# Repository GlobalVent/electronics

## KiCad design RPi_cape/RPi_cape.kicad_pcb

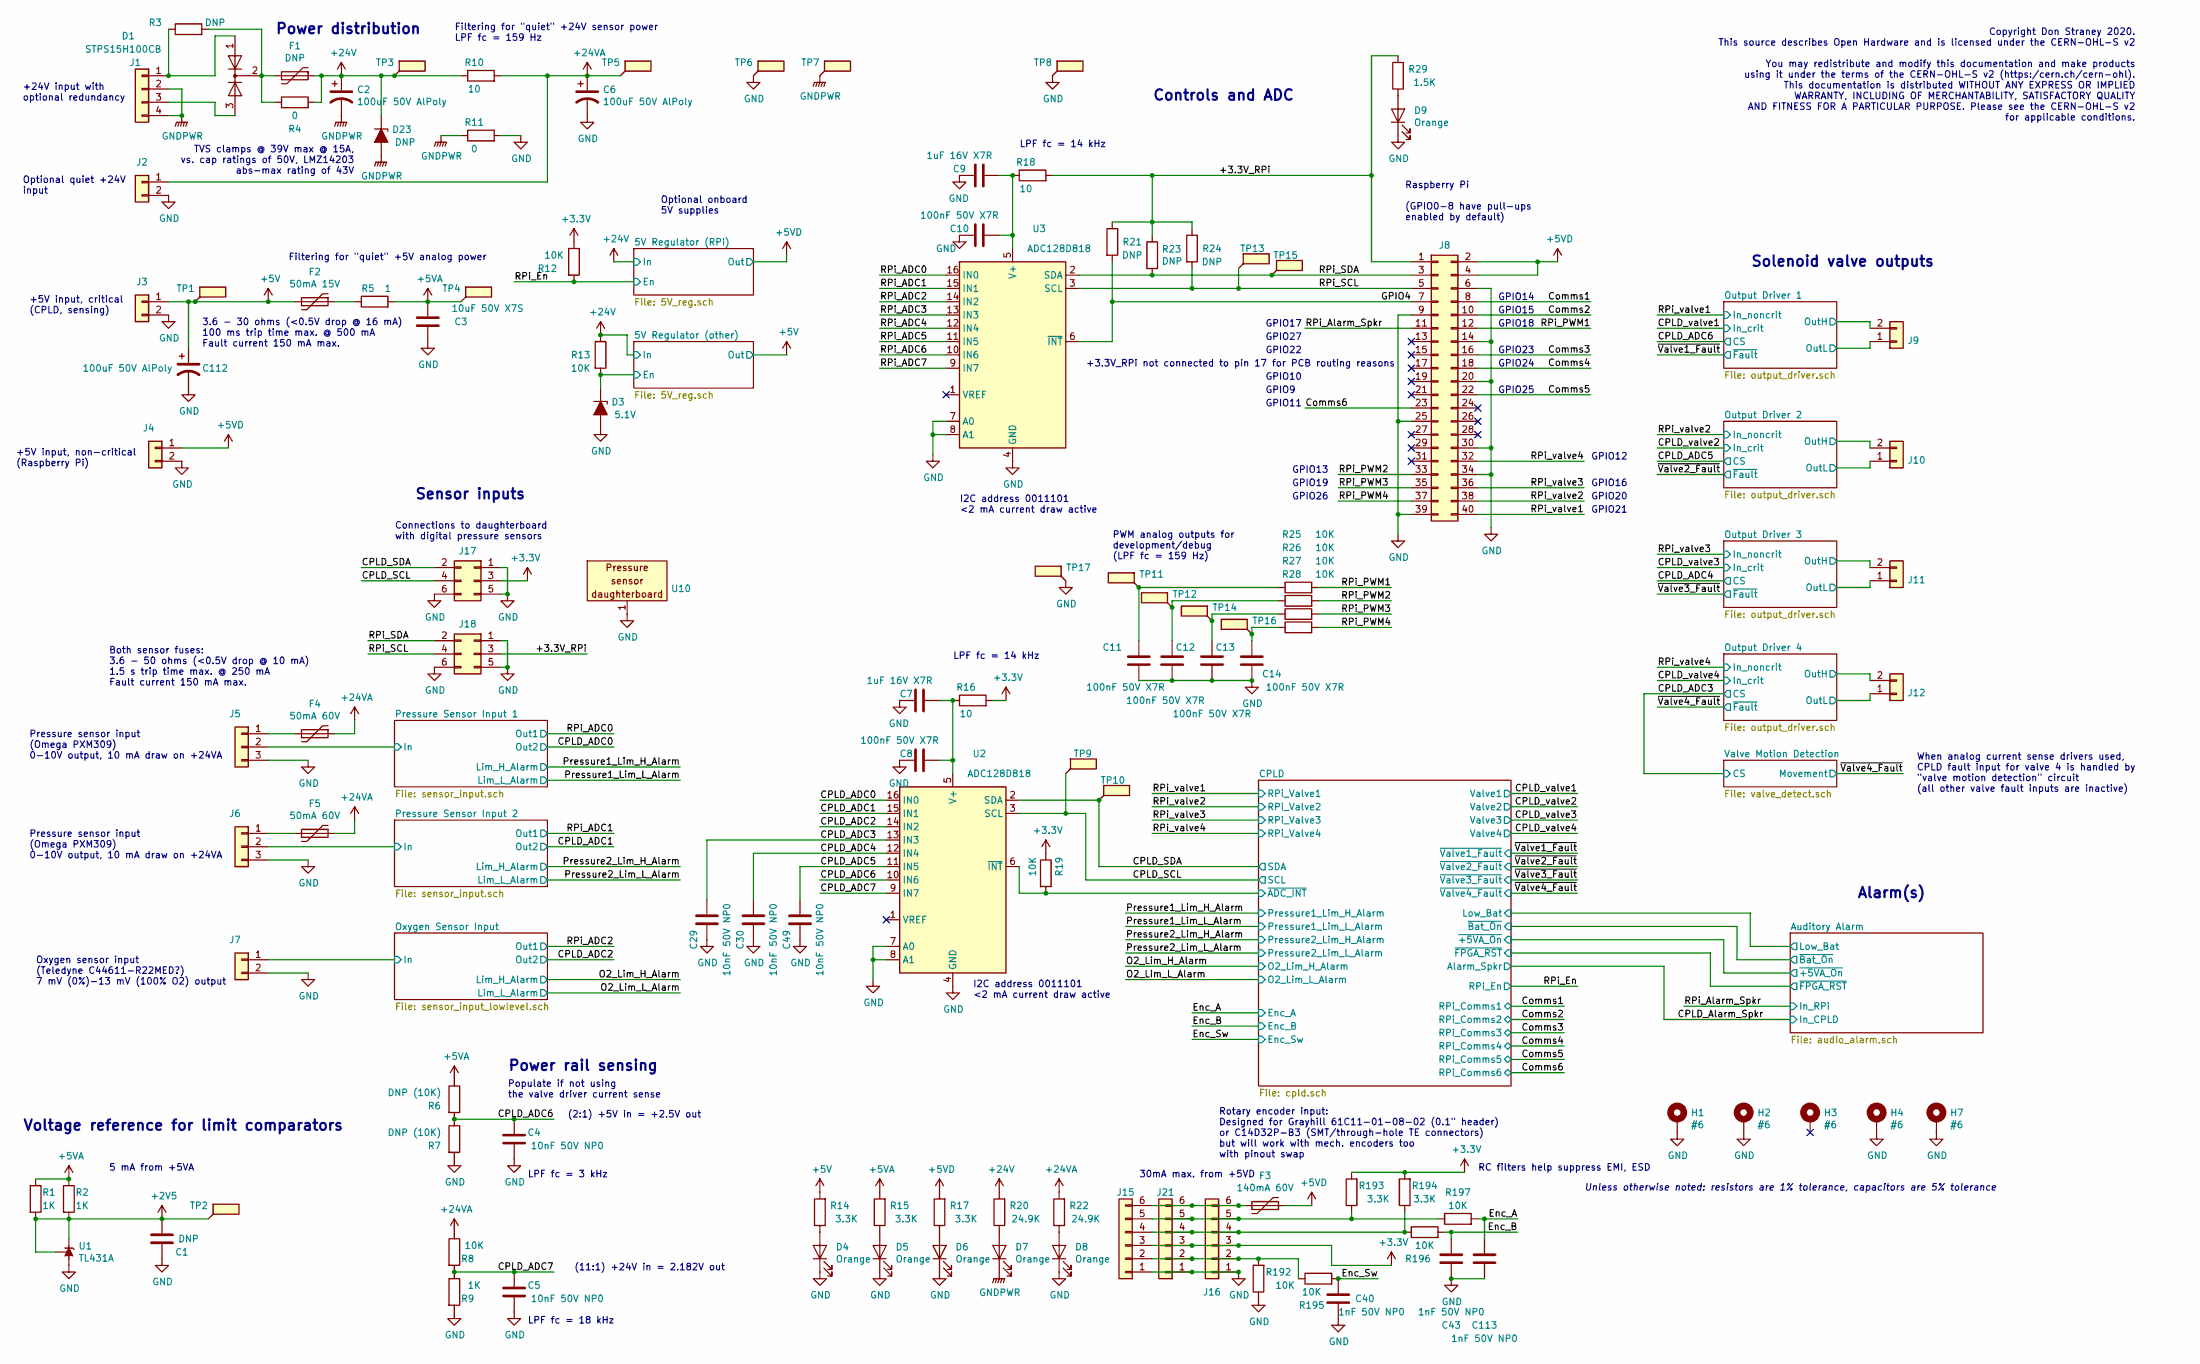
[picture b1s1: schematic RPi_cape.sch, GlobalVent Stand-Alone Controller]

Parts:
C1: DNP; C_0805_2012Metric
C2, C6, C112: 100uF 50V AlPoly; CP_Elec_10x10.5; Part Number EEH-ZC1H101P
C3: 10uF 50V X7S; C_1210_3225Metric; Part Number GCM32EC71H106KA03L
C4, C5, C29, C30, C49: 10nF 50V NP0; C_0603_1608Metric; Part Number GRM1885C1H103JA01D
C7, C9: 1uF 16V X7R; C_0805_2012Metric; Part Number C0805C105K4RACTU
C8, C10, C11, C12, C13, C14: 100nF 50V X7R; C_0603_1608Metric; Part Number 06035C104JAT2A
C40, C43, C113: 1nF 50V NP0; C_0603_1608Metric; Part Number 06035A102JAT2A
D1: STPS15H100CB; TO-252-2; Part Number STPS15H100CB-TR
D3: 5.1V; D_SOD-123; Part Number MMSZ5231BT1G
D4, D5, D6, D7, D8, D9: Orange; LED_0805_2012Metric; Part Number HSMD-C170
D23: DNP; D_SMB; Part Number SMBJ24A
F1: DNP; Fuse_2920_7451Metric
F2: 50mA 15V; Fuse_0603_1608Metric; Part Number 0ZCM0005FF2G
F3: 140mA 60V; Fuse_1812_4532Metric; Part Number 0ZCG0014FF2C
F4, F5: 50mA 60V; Fuse_1206_3216Metric; Part Number 0ZCJ0005FF2E
H1, H2, H3, H4, H7: #6; MountingHole_3.7mm_Pad_Via
J1: Conn_01x04; Connector_Spring_Phoenix_1985218; Part Number 1985218
J2, J3, J4, J7, J9, J10, J11, J12: Conn_01x02; Connector_Spring_Phoenix_1985195; Part Number 1985195
J5, J6: Conn_01x03; Connector_Spring_Phoenix_1985205; Part Number 1985205
J8: Conn_02x20_Odd_Even; PinSocket_2x20_P2.54mm_Vertical; Part Number PPPC202LFBN-RC
J15: Conn_01x06; TE_188275-6; Part Number 188275-6
J16: Conn_01x06; PinSocket_1x06_P2.54mm_Vertical
J17, J18: Conn_02x03_Odd_Even; PinHeader_2x03_P2.54mm_Vertical_SMD; Part Number 1241050-3
J21: Conn_01x06; TE_215079-6; Part Number 215079-6
R1, R2, R9: 1K; R_1206_3216Metric; Part Number RK73H2BTTD1001F
R3, R21, R23, R24: DNP; R_1206_3216Metric
R4, R11: 0; R_1206_3216Metric; Part Number ERJ-8GEY0R00V
R5: 1; R_1206_3216Metric; Part Number ERJ-8RQF1R0V
R6, R7: DNP (10K); R_1206_3216Metric; Part Number RK73H2BTTD1002F
R8, R12, R13, R19, R25, R26, R27, R28, R192, R195, R196, R197: 10K; R_1206_3216Metric; Part Number RK73H2BTTD1002F
R10, R16, R18: 10; R_1206_3216Metric; Part Number RK73H2BTTD10R0F
R14, R15, R17, R193, R194: 3.3K; R_1206_3216Metric; Part Number RK73H2BTTD3301F
R20, R22: 24.9K; R_1206_3216Metric; Part Number RK73H2BTTD2492F
R29: 1.5K; R_1206_3216Metric; Part Number RK73H2BTTD1501F
TP1, TP2, TP3, TP4, TP5, TP6, TP7, TP8, TP9, TP10, TP11, TP12, TP13, TP14, TP15, TP16, TP17: TestPoint_Flag; TestPoint_Keystone_5019_Minature; Part Number 5019
U1: TL431A; SOT-23; Part Number TL431AQDBZR,215
U2, U3: ADC128D818; TSSOP-16_4.4x5mm_P0.65mm; Part Number ADC128D818CIMTX/NOPB
U10: Pressure_sensor_daughterboard; Pressure_sensor_daughterboard_1.2

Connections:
+2V5: C1.2, R1.2, R2.2, TP2.1, U1.1 (K), U1.2 (REF); also elsewhere on the board
+3V3: J15.3, J16.3, J17.3, J21.3, R12.1, R16.2, R19.1, R193.2, R194.2; also elsewhere on the board
+5V: C112.1, F2.2, J3.1, R14.2, TP1.1; also elsewhere on the board
+5VD: F3.1, J4.1, J8.2, J8.4, R17.2; also elsewhere on the board
+24V: C2.1, D23.1 (K), F1.1, R4.2, R10.1, R13.1, R20.2, TP3.1; also elsewhere on the board
+24VA: C6.1, F4.1, F5.1, J2.1, R8.1, R10.2, R22.2, TP5.1; also elsewhere on the board
/5V Regulator (other)/En: D3.1 (K), R13.2; also elsewhere on the board
/+3.3V_RPi: J8.1, J18.3, R18.2, R21.1, R23.1, R24.1, R29.2
/CPLD/~ADC_INT: R19.2, U2.6 (~INT); also elsewhere on the board
/CPLD_ADC0: U2.16 (IN0); also elsewhere on the board
/CPLD_ADC1: U2.15 (IN1); also elsewhere on the board
/CPLD_ADC2: U2.14 (IN2); also elsewhere on the board
/CPLD_ADC4: C30.2, U2.12 (IN4); also elsewhere on the board
/CPLD_ADC5: C49.2, U2.11 (IN5); also elsewhere on the board
/CPLD_ADC6: C4.2, R6.2, R7.1, U2.10 (IN6); also elsewhere on the board
/CPLD_ADC7: C5.2, R8.2, R9.1, U2.9 (IN7)
/CPLD_SCL: J17.4, TP9.1, U2.3 (SCL); also elsewhere on the board
/CPLD_SDA: J17.2, TP10.1, U2.2 (SDA); also elsewhere on the board
/Comms1: J8.8; also elsewhere on the board
/Comms2: J8.10; also elsewhere on the board
/Comms3: J8.16; also elsewhere on the board
/Comms4: J8.18; also elsewhere on the board
/Comms5: J8.22; also elsewhere on the board
/Comms6: J8.23; also elsewhere on the board
/Enc_A: C113.2, R197.2; also elsewhere on the board
/Enc_B: C43.2, R196.2; also elsewhere on the board
/Enc_Sw: C40.2, R195.2; also elsewhere on the board
/GPIO4: J8.7, R21.2, U3.6 (~INT)
/Output Driver 1/OutH: J9.2; also elsewhere on the board
/Output Driver 1/OutL: J9.1; also elsewhere on the board
/Output Driver 2/OutH: J10.2; also elsewhere on the board
/Output Driver 2/OutL: J10.1; also elsewhere on the board
/Output Driver 3/OutH: J11.2; also elsewhere on the board
/Output Driver 3/OutL: J11.1; also elsewhere on the board
/Output Driver 4/OutH: J12.2; also elsewhere on the board
/Output Driver 4/OutL: J12.1; also elsewhere on the board
/Oxygen Sensor Input/In: J7.1; also elsewhere on the board
/Pressure Sensor Input 1/In: J5.2; also elsewhere on the board
/Pressure Sensor Input 2/In: J6.2; also elsewhere on the board
/RPi_ADC0: U3.16 (IN0); also elsewhere on the board
/RPi_ADC1: U3.15 (IN1); also elsewhere on the board
/RPi_ADC2: U3.14 (IN2); also elsewhere on the board
/RPi_ADC3: U3.13 (IN3)
/RPi_ADC4: U3.12 (IN4)
/RPi_ADC5: U3.11 (IN5)
/RPi_ADC6: U3.10 (IN6)
/RPi_ADC7: U3.9 (IN7)
/RPi_Alarm_Spkr: J8.11; also elsewhere on the board
/RPi_En: R12.2; also elsewhere on the board
/RPi_PWM1: J8.12, R25.2
/RPi_PWM2: J8.33, R26.2
/RPi_PWM3: J8.35, R27.2
/RPi_PWM4: J8.37, R28.2
/RPi_SCL: J8.5, J18.4, R24.2, TP13.1, U3.3 (SCL)
/RPi_SDA: J8.3, J18.2, R23.2, TP15.1, U3.2 (SDA)
/RPi_valve1: J8.40; also elsewhere on the board
/RPi_valve2: J8.38; also elsewhere on the board
/RPi_valve3: J8.36; also elsewhere on the board
/RPi_valve4: J8.32; also elsewhere on the board
GNDPWR: C2.2, D7.1 (K), D23.2 (A), J1.2, J1.4, R11.1, TP7.1; also elsewhere on the board
unnamed: C7.2, C8.2, R16.1, U2.5 (V+)
unnamed: C9.2, C10.2, R18.1, U3.5 (V+)
unnamed: C11.1, R25.1, TP11.1
unnamed: C12.1, R26.1, TP12.1
unnamed: C13.1, R27.1, TP14.1
unnamed: C14.1, R28.1, TP16.1
unnamed: D1.1 (A), J1.1, R3.1
unnamed: D1.2 (K), F1.2, R3.2, R4.1
unnamed: D1.3 (A), J1.3
unnamed: D4.2 (A), R14.1
unnamed: D5.2 (A), R15.1
unnamed: D6.2 (A), R17.1
unnamed: D7.2 (A), R20.1
unnamed: D8.2 (A), R22.1
unnamed: D9.2 (A), R29.1
unnamed: F2.1, R5.1
unnamed: F3.2, J15.6, J16.6, J21.6
unnamed: F4.2, J5.1
unnamed: F5.2, J6.1
unnamed: J15.2, J16.2, J21.2, R192.2, R195.1
unnamed: J15.4, J16.4, J21.4, R194.1, R196.1
unnamed: J15.5, J16.5, J21.5, R193.1, R197.1

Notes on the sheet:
Raspberry Pi (GPIO0-8 have pull-ups enabled by default)
I2C address 0011101 <2 mA current draw active
Optional quiet +24V input
+24V input with optional redundancy
+5V input, critical (CPLD, sensing)
Filtering for "quiet" +24V sensor power LPF fc = 159 Hz
Filtering for "quiet" +5V analog power
(2:1) +5V in = +2.5V out
(11:1) +24V in = 2.182V out
LPF fc = 3 kHz
LPF fc = 18 kHz
Pressure sensor input (Omega PXM309) 0-10V output, 10 mA draw on +24VA
Oxygen sensor input (Teledyne C44611-R22MED?) 7 mV (0%)-13 mV (100% O2) output
Power rail sensing
Sensor inputs
Power distribution
Solenoid valve outputs
Controls and ADC
+5V input, non-critical (Raspberry Pi)
PWM analog outputs for development/debug (LPF fc = 159 Hz)
Both sensor fuses: 3.6 - 50 ohms (<0.5V drop @ 10 mA) 1.5 s trip time max. @ 250 mA Fault current 150 mA max.
LPF fc = 14 kHz
GPIO17
GPIO27
GPIO22
GPIO10
Voltage reference for limit comparators
5 mA from +5VA
3.6 - 30 ohms (<0.5V drop @ 16 mA) 100 ms trip time max. @ 500 mA Fault current 150 mA max.
GPIO9
Optional onboard 5V supplies
GPIO15
GPIO18
GPIO24
GPIO14
GPIO23
GPIO25
Unless otherwise noted: resistors are 1% tolerance, capacitors are 5% tolerance
GPIO13
GPIO19

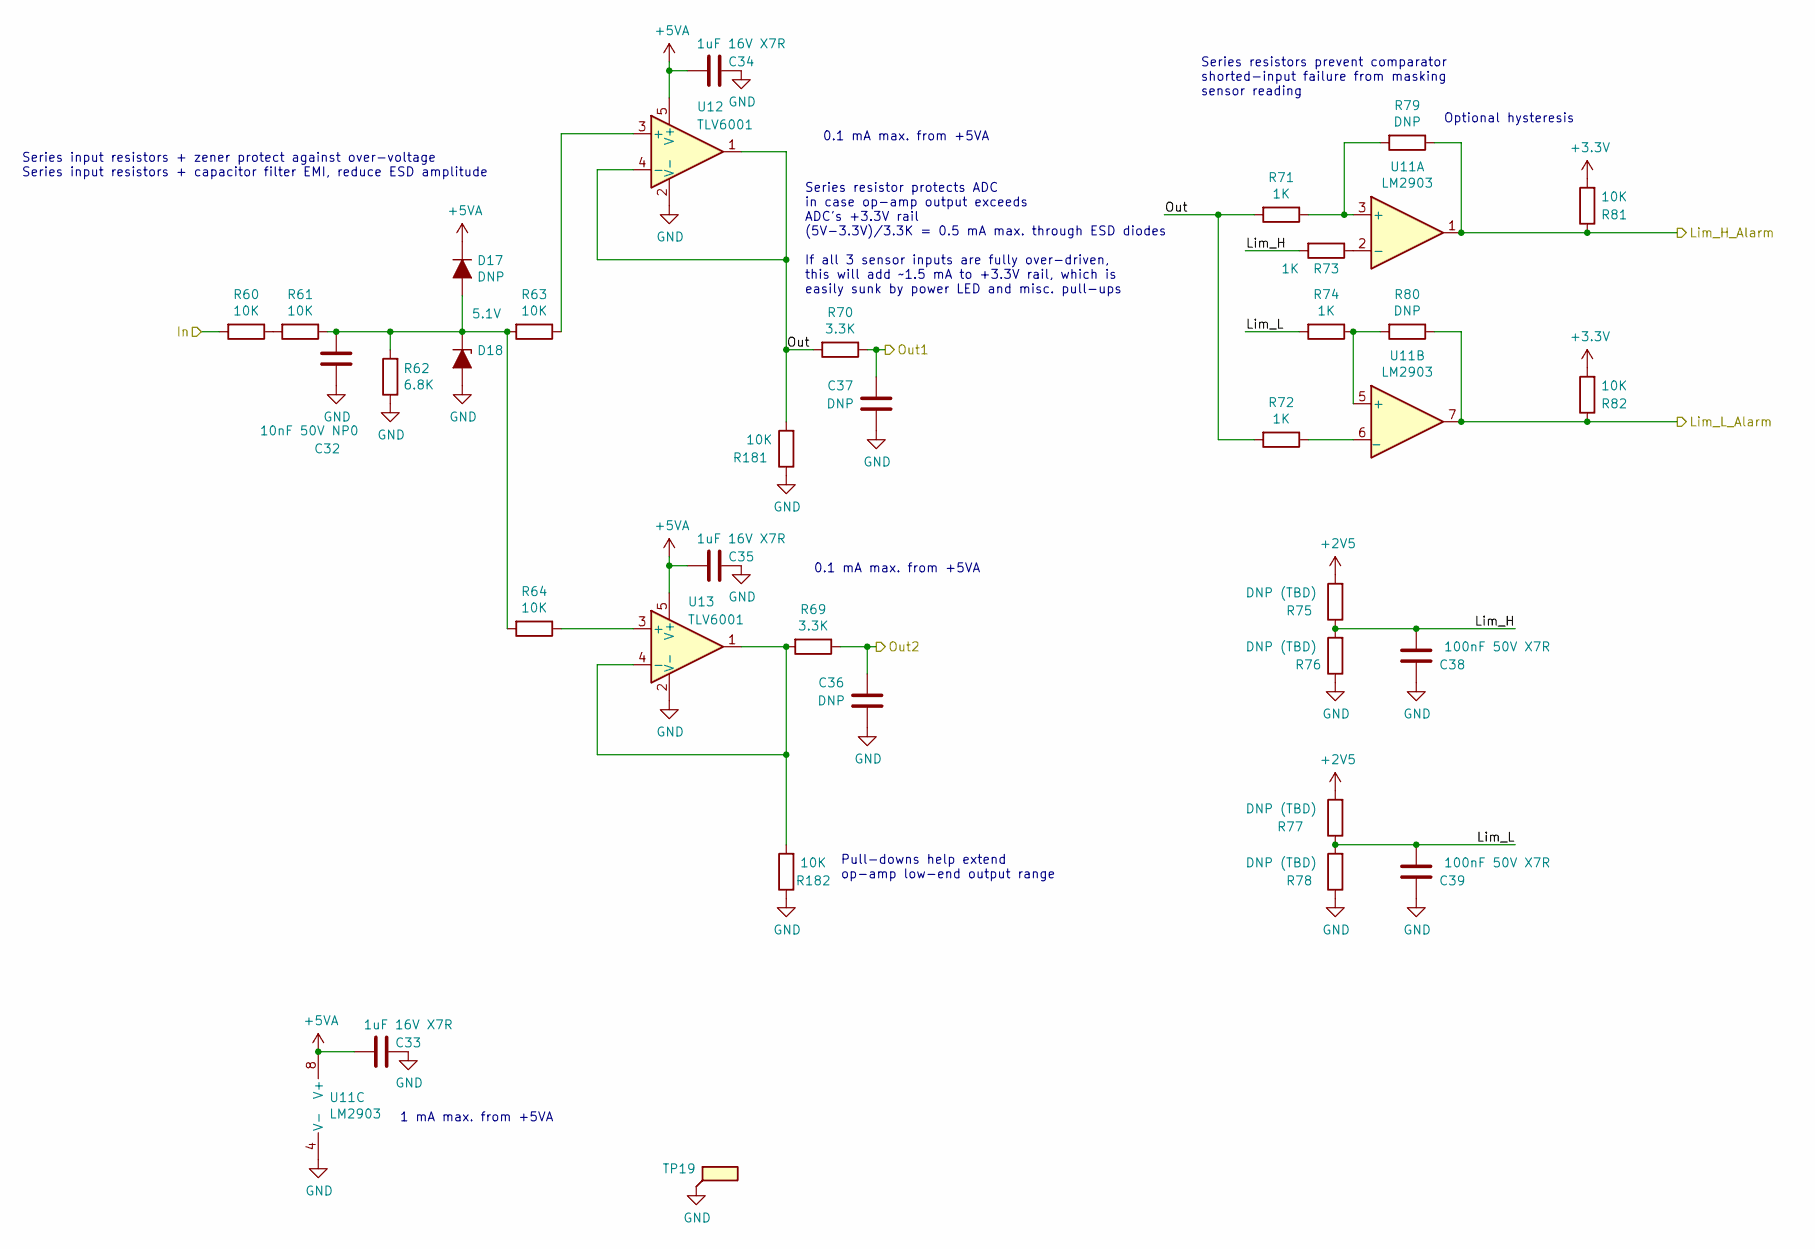
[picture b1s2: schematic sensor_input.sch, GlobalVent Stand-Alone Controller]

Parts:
C20: 10nF 50V NP0; C_0603_1608Metric; Part Number GRM1885C1H103JA01D
C21, C22, C23: 1uF 16V X7R; C_0805_2012Metric; Part Number C0805C105K4RACTU
C24, C25: DNP; C_0603_1608Metric
C26, C27: 100nF 50V X7R; C_0603_1608Metric; Part Number 06035C104JAT2A
D10: DNP; D_SOD-123
D11: 5.1V; D_SOD-123; Part Number MMSZ5231BT1G
R30, R31, R33, R34, R51, R52, R179, R180: 10K; R_1206_3216Metric; Part Number RK73H2BTTD1002F
R32: 6.8K; R_1206_3216Metric; Part Number RK73H2BTTD6801F
R39, R40: 3.3K; R_1206_3216Metric; Part Number RK73H2BTTD3301F
R41, R42, R43, R44: 1K; R_1206_3216Metric; Part Number RK73H2BTTD1001F
R45, R46, R47, R48: DNP (TBD); R_1206_3216Metric
R49, R50: DNP; R_1206_3216Metric
TP18: TestPoint_Flag; TestPoint_Keystone_5019_Minature; Part Number 5019
U5: LM2903; VSSOP-8_3.0x3.0mm_P0.65mm; Part Number LM2903DGKR
U6, U7: TLV6001; SOT-23-5; Part Number TLV6001IDBVR

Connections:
+2V5: R45.2, R47.2; also elsewhere on the board
+3V3: R51.2, R52.2; also elsewhere on the board
/CPLD_ADC0: C24.2, R39.1; also elsewhere on the board
/Pressure1_Lim_H_Alarm: R49.1, R51.1, U5.1; also elsewhere on the board
/Pressure1_Lim_L_Alarm: R50.1, R52.1, U5.7; also elsewhere on the board
/Pressure Sensor Input 1/In: R30.2; also elsewhere on the board
/Pressure Sensor Input 1/Lim_H: C26.2, R43.2, R45.1, R46.2
/Pressure Sensor Input 1/Lim_L: C27.2, R44.2, R47.1, R48.2
/Pressure Sensor Input 1/Out: R40.2, R41.2, R42.2, R179.2, U6.1, U6.4 (-)
/RPi_ADC0: C25.2, R40.1; also elsewhere on the board
unnamed: C20.2, D10.2 (A), D11.1 (K), R31.1, R32.2, R33.2, R34.2
unnamed: R30.1, R31.2
unnamed: R33.1, U6.3 (+)
unnamed: R34.1, U7.3 (+)
unnamed: R41.1, R49.2, U5.3 (+)
unnamed: R42.1, U5.6 (_)
unnamed: R43.1, U5.2 (-)
unnamed: R44.1, R50.2, U5.5 (+)
unnamed: R39.2, R180.2, U7.1, U7.4 (-)

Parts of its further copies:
C32: 10nF 50V NP0; C_0603_1608Metric; Part Number GRM1885C1H103JA01D
C33, C34, C35: 1uF 16V X7R; C_0805_2012Metric; Part Number C0805C105K4RACTU
C36, C37: DNP; C_0603_1608Metric
C38, C39: 100nF 50V X7R; C_0603_1608Metric; Part Number 06035C104JAT2A
D17: DNP; D_SOD-123
D18: 5.1V; D_SOD-123; Part Number MMSZ5231BT1G
R60, R61, R63, R64, R81, R82, R181, R182: 10K; R_1206_3216Metric; Part Number RK73H2BTTD1002F
R62: 6.8K; R_1206_3216Metric; Part Number RK73H2BTTD6801F
R69, R70: 3.3K; R_1206_3216Metric; Part Number RK73H2BTTD3301F
R71, R72, R73, R74: 1K; R_1206_3216Metric; Part Number RK73H2BTTD1001F
R75, R76, R77, R78: DNP (TBD); R_1206_3216Metric
R79, R80: DNP; R_1206_3216Metric
TP19: TestPoint_Flag; TestPoint_Keystone_5019_Minature; Part Number 5019
U11: LM2903; VSSOP-8_3.0x3.0mm_P0.65mm; Part Number LM2903DGKR
U12, U13: TLV6001; SOT-23-5; Part Number TLV6001IDBVR

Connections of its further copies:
+2V5: R75.2, R77.2; also elsewhere on the board
+3V3: R81.2, R82.2; also elsewhere on the board
/CPLD_ADC1: C36.2, R69.1; also elsewhere on the board
/Pressure2_Lim_H_Alarm: R79.1, R81.1, U11.1; also elsewhere on the board
/Pressure2_Lim_L_Alarm: R80.1, R82.1, U11.7; also elsewhere on the board
/Pressure Sensor Input 2/In: R60.2; also elsewhere on the board
/Pressure Sensor Input 2/Lim_H: C38.2, R73.2, R75.1, R76.2
/Pressure Sensor Input 2/Lim_L: C39.2, R74.2, R77.1, R78.2
/Pressure Sensor Input 2/Out: R70.2, R71.2, R72.2, R181.2, U12.1, U12.4 (-)
/RPi_ADC1: C37.2, R70.1; also elsewhere on the board
unnamed: C32.2, D17.2 (A), D18.1 (K), R61.1, R62.2, R63.2, R64.2
unnamed: R60.1, R61.2
unnamed: R63.1, U12.3 (+)
unnamed: R64.1, U13.3 (+)
unnamed: R71.1, R79.2, U11.3 (+)
unnamed: R72.1, U11.6 (_)
unnamed: R73.1, U11.2 (-)
unnamed: R74.1, R80.2, U11.5 (+)
unnamed: R69.2, R182.2, U13.1, U13.4 (-)

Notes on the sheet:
Series resistor protects ADC in case op-amp output exceeds ADC's +3.3V rail (5V-3.3V)/3.3K = 0.5 mA max. through ESD diodes If all 3 sensor inputs are fully over-driven, this will add ~~1.5 mA to +3.3V rail, which is easily sunk by power LED and misc. pull-ups
Series resistors prevent comparator shorted-input failure from masking sensor reading
Optional hysteresis
1 mA max. from +5VA
0.1 mA max. from +5VA
Series input resistors + zener protect against over-voltage Series input resistors + capacitor filter EMI, reduce ESD amplitude
Pull-downs help extend op-amp low-end output range

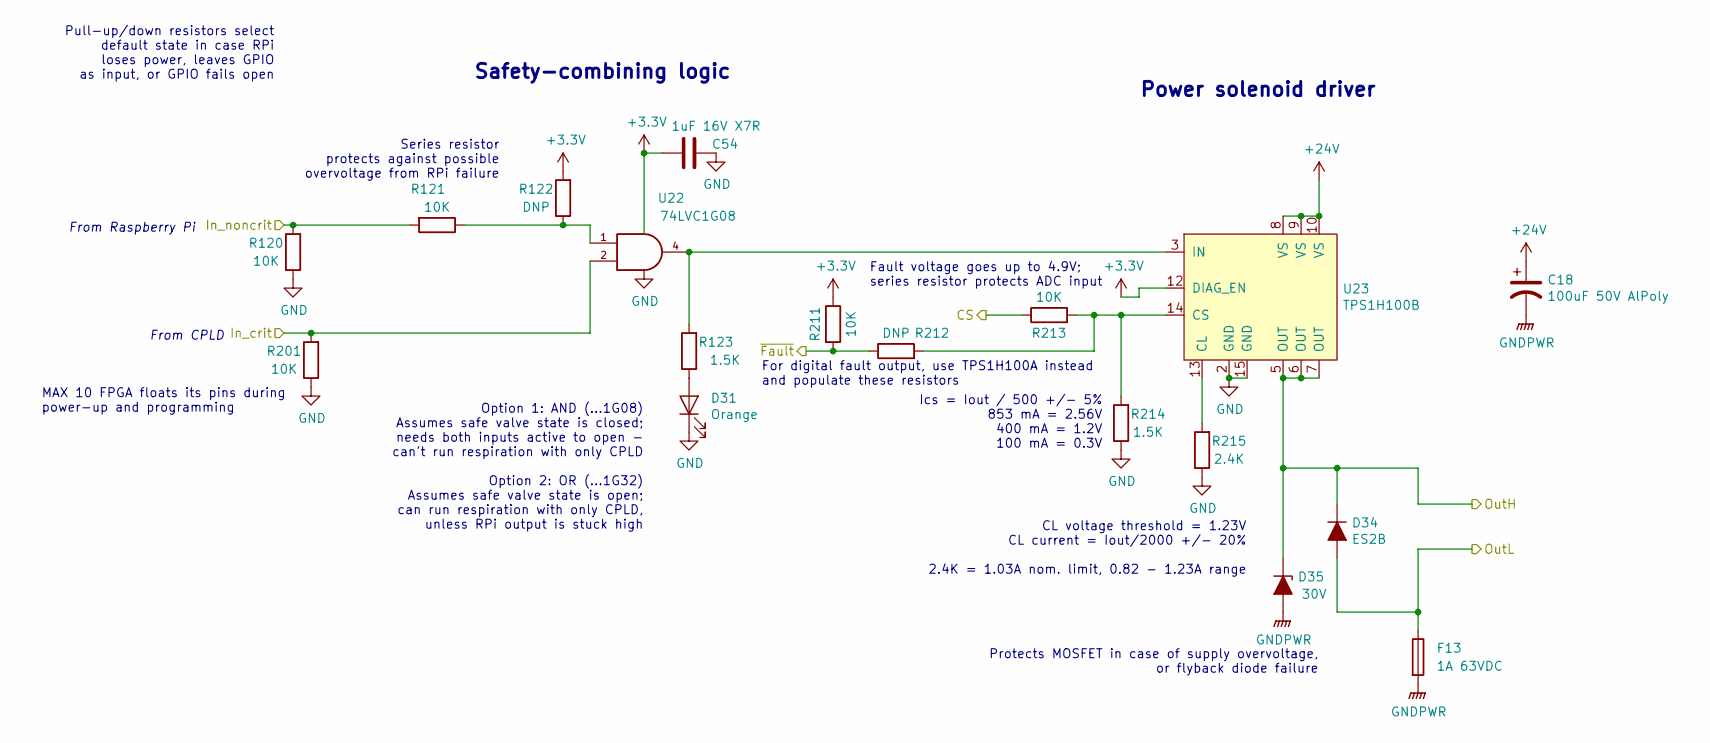
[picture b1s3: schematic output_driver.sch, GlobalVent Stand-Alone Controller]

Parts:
C16: 100uF 50V AlPoly; CP_Elec_10x10.5; Part Number EEH-ZC1H101P
C28: 1uF 16V X7R; C_0805_2012Metric; Part Number C0805C105K4RACTU
D12: Orange; LED_0805_2012Metric; Part Number HSMD-C170
D15: ES2B; D_SMA; Part Number ES2G-E3/52T
D16: 30V; D_SMA; Part Number SMAJ30A-E3/61
F10: 1A 63VDC; Fuse_1206_3216Metric; Part Number SF-1206FP100-2
R53, R54, R57, R59, R198: 10K; R_1206_3216Metric; Part Number RK73H2BTTD1002F
R55, R58: DNP; R_1206_3216Metric
R56, R110: 1.5K; R_1206_3216Metric; Part Number RK73H2BTTD1501F
R111: 2.4K; R_1206_3216Metric; Part Number RK73H2BTTD2401F
U8: 74LVC1G08; SOT-23-5; Part Number SN74LVC1G08DBVR
U9: TPS1H100B; TSSOP-14-1EP_4.4x5mm_P0.65mm; Part Number TPS1H100BQPWPRQ1

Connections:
+3V3: C28.2, R55.2, R57.1, U8.5 (VCC), U9.12 (DIAG_EN); also elsewhere on the board
+24V: C16.1, U9.8 (VS), U9.9 (VS), U9.10 (VS); also elsewhere on the board
/CPLD_ADC6: R59.1; also elsewhere on the board
/CPLD_valve1: R198.2, U8.2; also elsewhere on the board
/Output Driver 1/OutH: D15.1 (K), D16.1 (K), U9.5 (OUT), U9.6 (OUT), U9.7 (OUT); also elsewhere on the board
/Output Driver 1/OutL: D15.2 (A), F10.1; also elsewhere on the board
/RPi_valve1: R53.2, R54.2; also elsewhere on the board
/~Valve1_Fault: R57.2, R58.1; also elsewhere on the board
GNDPWR: C16.2, D16.2 (A), F10.2; also elsewhere on the board
unnamed: D12.2 (A), R56.1
unnamed: R54.1, R55.1, U8.1
unnamed: R56.2, U8.4, U9.3 (IN)
unnamed: R58.2, R59.2, R110.2, U9.14 (CS)
unnamed: R111.2, U9.13 (CL)

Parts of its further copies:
C15, C17, C18: 100uF 50V AlPoly; CP_Elec_10x10.5; Part Number EEH-ZC1H101P
C48, C51, C54: 1uF 16V X7R; C_0805_2012Metric; Part Number C0805C105K4RACTU
D21, D26, D31: Orange; LED_0805_2012Metric; Part Number HSMD-C170
D24, D29, D34: ES2B; D_SMA; Part Number ES2G-E3/52T
D25, D30, D35: 30V; D_SMA; Part Number SMAJ30A-E3/61
F11, F12, F13: 1A 63VDC; Fuse_1206_3216Metric; Part Number SF-1206FP100-2
R106, R107, R112, R113, R114, R118, R120, R121, R125, R199, R200, R201, R208, R211, R213: 10K; R_1206_3216Metric; Part Number RK73H2BTTD1002F
R108, R115, R117, R122, R126, R212: DNP; R_1206_3216Metric
R109, R116, R119, R123, R209, R214: 1.5K; R_1206_3216Metric; Part Number RK73H2BTTD1501F
R124, R210, R215: 2.4K; R_1206_3216Metric; Part Number RK73H2BTTD2401F
U18, U20, U22: 74LVC1G08; SOT-23-5; Part Number SN74LVC1G08DBVR
U19, U21, U23: TPS1H100B; TSSOP-14-1EP_4.4x5mm_P0.65mm; Part Number TPS1H100BQPWPRQ1

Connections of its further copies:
+3V3: C48.2, C51.2, C54.2, R108.2, R112.1, R115.2, R122.2, R125.1, R211.1, U18.5 (VCC), U19.12 (DIAG_EN), U20.5 (VCC), U21.12 (DIAG_EN), U22.5 (VCC), U23.12 (DIAG_EN); also elsewhere on the board
+24V: C15.1, C17.1, C18.1, U19.8 (VS), U19.9 (VS), U19.10 (VS), U21.8 (VS), U21.9 (VS), U21.10 (VS), U23.8 (VS), U23.9 (VS), U23.10 (VS); also elsewhere on the board
/CPLD_ADC4: R208.1; also elsewhere on the board
/CPLD_ADC5: R118.1; also elsewhere on the board
/CPLD_valve2: R199.2, U18.2; also elsewhere on the board
/CPLD_valve3: R200.2, U20.2; also elsewhere on the board
/CPLD_valve4: R201.2, U22.2; also elsewhere on the board
/Output Driver 2/OutH: D24.1 (K), D25.1 (K), U19.5 (OUT), U19.6 (OUT), U19.7 (OUT); also elsewhere on the board
/Output Driver 2/OutL: D24.2 (A), F11.1; also elsewhere on the board
/Output Driver 3/OutH: D29.1 (K), D30.1 (K), U21.5 (OUT), U21.6 (OUT), U21.7 (OUT); also elsewhere on the board
/Output Driver 3/OutL: D29.2 (A), F12.1; also elsewhere on the board
/Output Driver 4/OutH: D34.1 (K), D35.1 (K), U23.5 (OUT), U23.6 (OUT), U23.7 (OUT); also elsewhere on the board
/Output Driver 4/OutL: D34.2 (A), F13.1; also elsewhere on the board
/RPi_valve2: R106.2, R107.2; also elsewhere on the board
/RPi_valve3: R113.2, R114.2; also elsewhere on the board
/RPi_valve4: R120.2, R121.2; also elsewhere on the board
/~Valve2_Fault: R112.2, R117.1; also elsewhere on the board
/~Valve3_Fault: R125.2, R126.1; also elsewhere on the board
GNDPWR: C15.2, C17.2, C18.2, D25.2 (A), D30.2 (A), D35.2 (A), F11.2, F12.2, F13.2; also elsewhere on the board
unnamed: D21.2 (A), R109.1
unnamed: D26.2 (A), R116.1
unnamed: D31.2 (A), R123.1
unnamed: R107.1, R108.1, U18.1
unnamed: R109.2, U18.4, U19.3 (IN)
unnamed: R114.1, R115.1, U20.1
unnamed: R116.2, U20.4, U21.3 (IN)
unnamed: R117.2, R118.2, R119.2, U19.14 (CS)
unnamed: R121.1, R122.1, U22.1
unnamed: R123.2, U22.4, U23.3 (IN)
unnamed: R124.2, U19.13 (CL)
unnamed: R126.2, R208.2, R209.2, U21.14 (CS)
unnamed: R210.2, U21.13 (CL)
unnamed: R212.2, R213.2, R214.2, U23.14 (CS)
unnamed: R215.2, U23.13 (CL)

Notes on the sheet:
Protects MOSFET in case of supply overvoltage, or flyback diode failure
From Raspberry Pi
From CPLD
Series resistor protects against possible overvoltage from RPi failure
Option 1: AND (...1G08) Assumes safe valve state is closed; needs both inputs active to open - can't run respiration with only CPLD Option 2: OR (...1G32) Assumes safe valve state is open; can run respiration with only CPLD, unless RPi output is stuck high
Safety-combining logic
Power solenoid driver
Pull-up/down resistors select default state in case RPi loses power, leaves GPIO as input, or GPIO fails open
CL voltage threshold = 1.23V CL current = Iout/2000 +/- 20% 2.4K = 1.03A nom. limit, 0.82 - 1.23A range
Ics = Iout / 500 +/- 5% 853 mA = 2.56V 400 mA = 1.2V 100 mA = 0.3V
Fault voltage goes up to 4.9V; series resistor protects ADC input
For digital fault output, use TPS1H100A instead and populate these resistors
MAX 10 FPGA floats its pins during power-up and programming

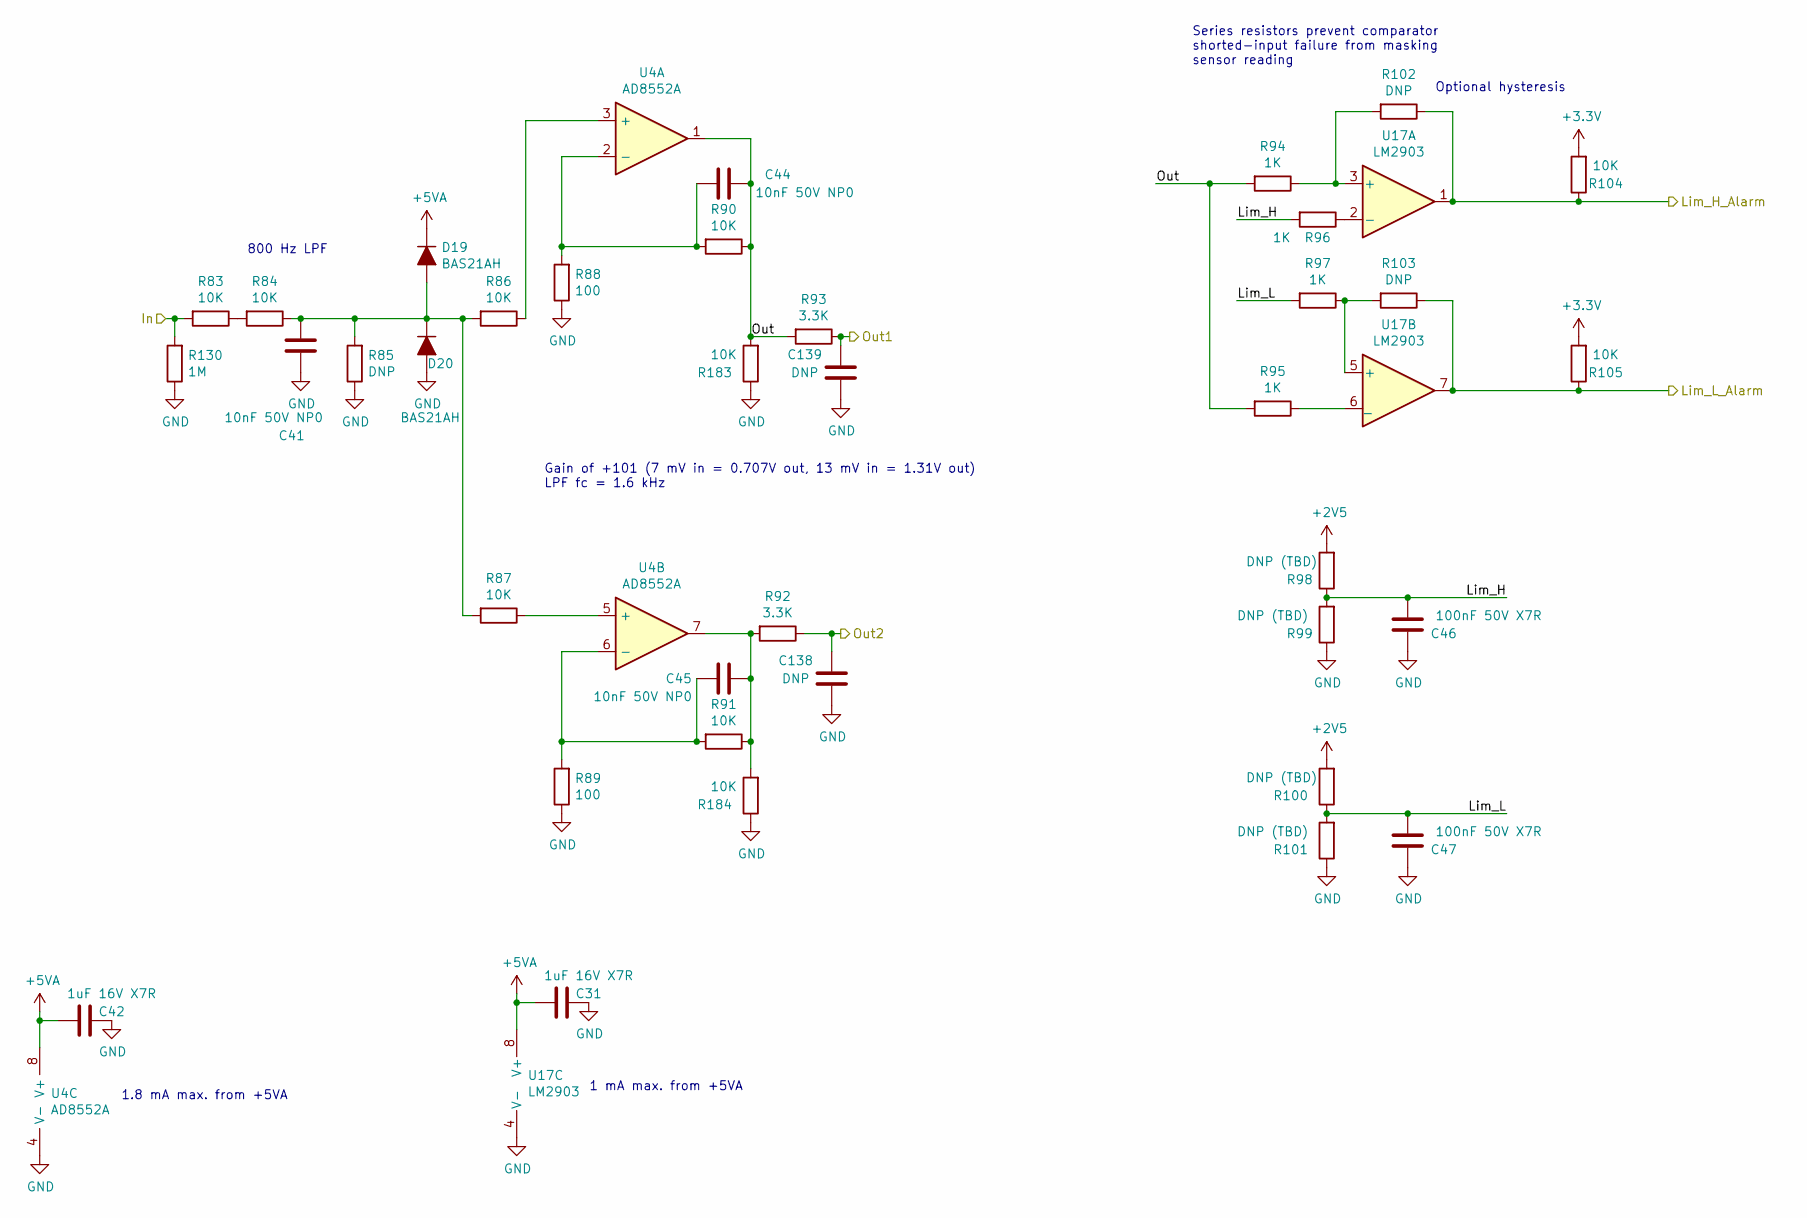
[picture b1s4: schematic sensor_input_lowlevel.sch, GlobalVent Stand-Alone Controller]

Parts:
C31, C42: 1uF 16V X7R; C_0805_2012Metric; Part Number C0805C105K4RACTU
C41, C44, C45: 10nF 50V NP0; C_0603_1608Metric; Part Number GRM1885C1H103JA01D
C46, C47: 100nF 50V X7R; C_0603_1608Metric; Part Number 06035C104JAT2A
C138, C139: DNP; C_0603_1608Metric
D19, D20: BAS21AH; D_SOD-323; Part Number BAS21AHT1G
R83, R84, R86, R87, R90, R91, R104, R105, R183, R184: 10K; R_1206_3216Metric; Part Number RK73H2BTTD1002F
R85, R102, R103: DNP; R_1206_3216Metric
R88, R89: 100; R_1206_3216Metric; Part Number RK73H2BTTD1000F
R92, R93: 3.3K; R_1206_3216Metric; Part Number RK73H2BTTD3301F
R94, R95, R96, R97: 1K; R_1206_3216Metric; Part Number RK73H2BTTD1001F
R98, R99, R100, R101: DNP (TBD); R_1206_3216Metric
R130: 1M; R_1206_3216Metric; Part Number RK73H2BTTD1004F
U4: AD8552A; SOIC-8_3.9x4.9mm_P1.27mm; Part Number AD8552ARZ-REEL
U17: LM2903; VSSOP-8_3.0x3.0mm_P0.65mm; Part Number LM2903DGKR

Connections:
+2V5: R98.2, R100.2; also elsewhere on the board
+3V3: R104.2, R105.2; also elsewhere on the board
/CPLD_ADC2: C138.2, R92.1; also elsewhere on the board
/O2_Lim_H_Alarm: R102.1, R104.1, U17.1; also elsewhere on the board
/O2_Lim_L_Alarm: R103.1, R105.1, U17.7; also elsewhere on the board
/Oxygen Sensor Input/In: R83.2, R130.2; also elsewhere on the board
/Oxygen Sensor Input/Lim_H: C46.2, R96.2, R98.1, R99.2
/Oxygen Sensor Input/Lim_L: C47.2, R97.2, R100.1, R101.2
/Oxygen Sensor Input/Out: C44.1, R90.1, R93.2, R94.2, R95.2, R183.2, U4.1
/RPi_ADC2: C139.2, R93.1; also elsewhere on the board
unnamed: C41.2, D19.2 (A), D20.1 (K), R84.1, R85.2, R86.2, R87.2
unnamed: C44.2, R88.2, R90.2, U4.2 (-)
unnamed: C45.1, R91.1, R92.2, R184.2, U4.7
unnamed: C45.2, R89.2, R91.2, U4.6 (-)
unnamed: R83.1, R84.2
unnamed: R86.1, U4.3 (+)
unnamed: R87.1, U4.5 (+)
unnamed: R95.1, U17.6 (_)
unnamed: R96.1, U17.2 (-)
unnamed: R94.1, R102.2, U17.3 (+)
unnamed: R97.1, R103.2, U17.5 (+)

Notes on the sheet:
Gain of +101 (7 mV in = 0.707V out, 13 mV in = 1.31V out) LPF fc = 1.6 kHz
Series resistors prevent comparator shorted-input failure from masking sensor reading
Optional hysteresis
1.8 mA max. from +5VA
1 mA max. from +5VA
800 Hz LPF

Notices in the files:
Pressure_sensor_daughterboard-MS5607-MS5803/Pressure_sensor_daughterboard-MS5607-MS5803.kicad_pcb:
Licensed under CERN-OHL-S v2
